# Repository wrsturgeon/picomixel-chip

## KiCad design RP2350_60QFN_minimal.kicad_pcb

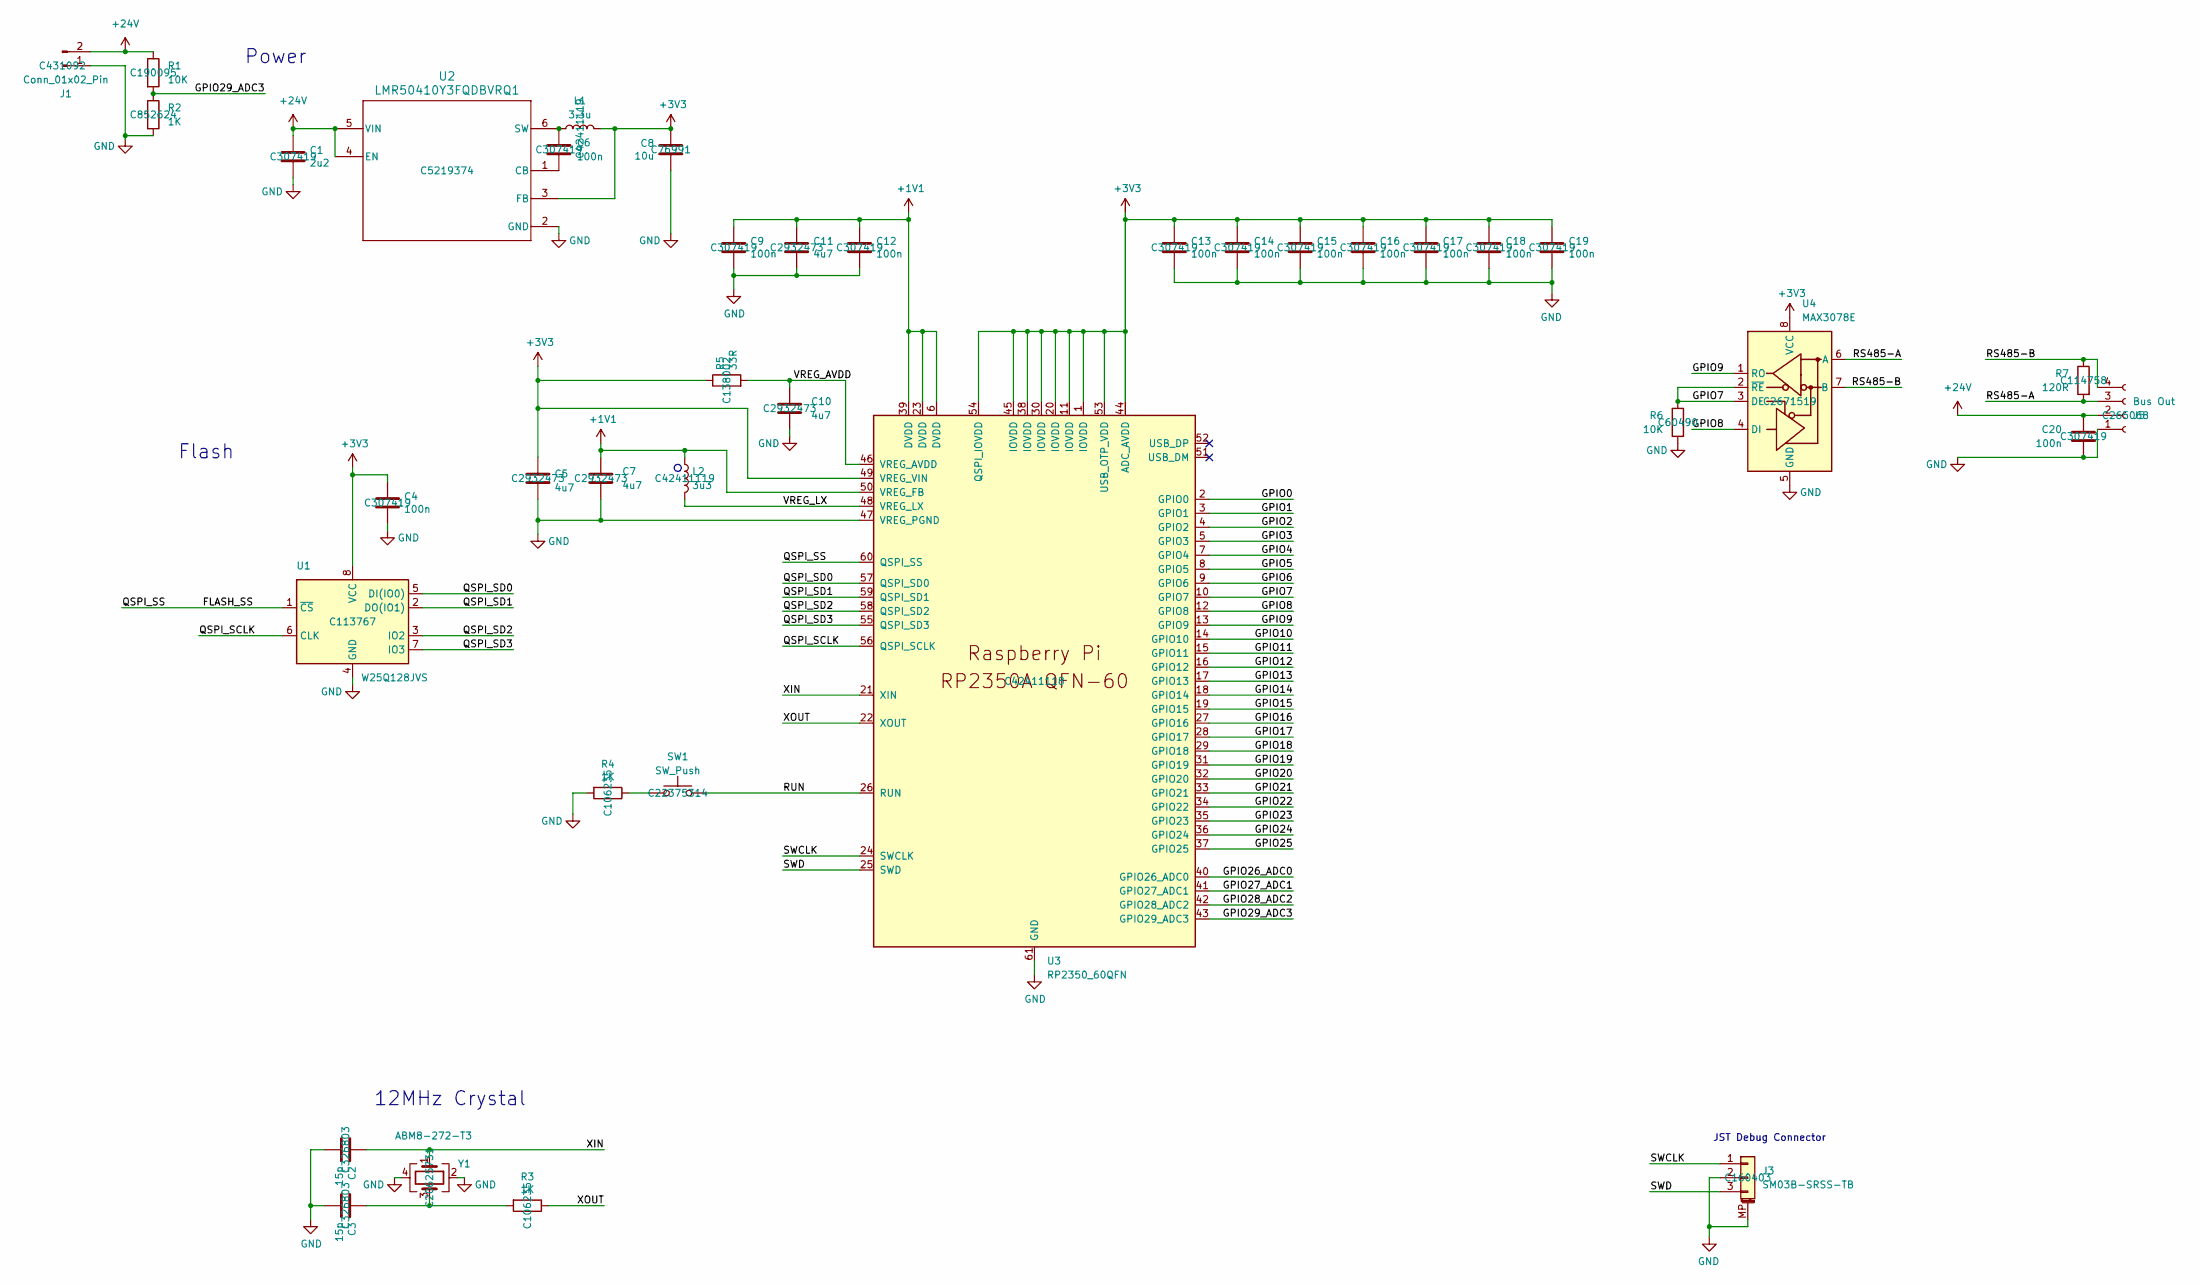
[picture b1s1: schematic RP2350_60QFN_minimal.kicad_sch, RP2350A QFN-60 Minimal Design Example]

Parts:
C1: 2u2; C_1206_3216Metric; LCSC Part # C307419
C2, C3: 15p; C_0402_1005Metric; LCSC Part # C326803
C4, C6, C9, C12, C13, C14, C16, C19, C20: 100n; C_0402_1005Metric; LCSC Part # C307419
C5, C7, C10, C11: 4u7; C_0402_1005Metric_small_pads; LCSC Part # C2932473
C8: 10u; C_0402_1005Metric; LCSC Part # C76991
C15, C17, C18: 100n; C_0402_1005Metric_small_pads; LCSC Part # C307419
J1: Conn_01x02_Pin; AMASS_XT30PW-M_1x02_P2.50mm_Horizontal; LCSC Part # C431092
J3: SM03B-SRSS-TB; JST_SH_SM03B-SRSS-TB_1x03-1MP_P1.00mm_Horizontal; LCSC Part # C160403
J5: Bus Out; JST_EH_S4B-EH_1x04_P2.50mm_Horizontal; LCSC Part # C265068
L1: 3.3u; L_pol_2016; LCSC Part # C42411119
L2: 3u3; L_pol_2016; LCSC Part # C42411119
R1: 10K; R_0402_1005Metric; LCSC Part # C190095
R2: 1K; R_0402_1005Metric; LCSC Part # C852624
R3, R4: 1K; R_0402_1005Metric; LCSC Part # C106235
R5: 33R; R_0402_1005Metric; LCSC Part # C138002
R6: 10K; R_0402_1005Metric; LCSC Part # C60490
R7: 120R; R_0402_1005Metric; LCSC Part # C114758
SW1: SW_Push; SW_Push_1P1T_NO_Vertical_Wuerth_434133025816; LCSC Part # C22375314
U1: W25Q128JVS; SOIC-8_5.3x5.3mm_P1.27mm; LCSC Part # C113767
U2: LMR50410Y3FQDBVRQ1; DBV0006A-MFG; LCSC Part # C5219374
U3: RP2350_60QFN; RP2350-QFN-60-1EP_7x7_P0.4mm_EP3.4x3.4mm_ThermalVias; LCSC Part # C42411118
U4: MAX3078E; SOIC-8_3.9x4.9mm_P1.27mm; LCSC Part # C2671519
Y1: ABM8-272-T3; Crystal_SMD_3225-4Pin_3.2x2.5mm; LCSC Part # C20625731

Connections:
+1V1: C7.1, C9.1, C11.1, C12.1, L2.1, U3.6 (DVDD), U3.23 (DVDD), U3.39 (DVDD), U3.50 (VREG_FB)
+3V3: C4.1, C5.1, C8.1, C13.1, C14.1, C15.1, C16.1, C17.1, C18.1, C19.1, L1.2, R5.1, U1.8 (VCC), U2.3 (FB), U3.1 (IOVDD), U3.11 (IOVDD), U3.20 (IOVDD), U3.30 (IOVDD), U3.38 (IOVDD), U3.44 (ADC_AVDD), U3.45 (IOVDD), U3.49 (VREG_VIN), U3.53 (USB_OTP_VDD), U3.54 (QSPI_IOVDD), U4.8 (VCC)
+24V: C1.1, C20.1, J1.2, J5.2, R1.1, U2.4 (EN), U2.5 (VIN)
/FLASH_SS: U1.1 (~CS), U3.60 (QSPI_SS)
/GPIO0: U3.2 (GPIO0)
/GPIO1: U3.3 (GPIO1)
/GPIO2: U3.4 (GPIO2)
/GPIO3: U3.5 (GPIO3)
/GPIO4: U3.7 (GPIO4)
/GPIO5: U3.8 (GPIO5)
/GPIO6: U3.9 (GPIO6)
/GPIO7: R6.1, U3.10 (GPIO7), U4.2 (~RE), U4.3 (DE)
/GPIO8: U3.12 (GPIO8), U4.4 (DI)
/GPIO9: U3.13 (GPIO9), U4.1 (RO)
/GPIO10: U3.14 (GPIO10)
/GPIO11: U3.15 (GPIO11)
/GPIO12: U3.16 (GPIO12)
/GPIO13: U3.17 (GPIO13)
/GPIO14: U3.18 (GPIO14)
/GPIO15: U3.19 (GPIO15)
/GPIO16: U3.27 (GPIO16)
/GPIO17: U3.28 (GPIO17)
/GPIO18: U3.29 (GPIO18)
/GPIO19: U3.31 (GPIO19)
/GPIO20: U3.32 (GPIO20)
/GPIO21: U3.33 (GPIO21)
/GPIO22: U3.34 (GPIO22)
/GPIO23: U3.35 (GPIO23)
/GPIO24: U3.36 (GPIO24)
/GPIO25: U3.37 (GPIO25)
/GPIO26_ADC0: U3.40 (GPIO26_ADC0)
/GPIO27_ADC1: U3.41 (GPIO27_ADC1)
/GPIO28_ADC2: U3.42 (GPIO28_ADC2)
/GPIO29_ADC3: R1.2, R2.1, U3.43 (GPIO29_ADC3)
/QSPI_SCLK: U1.6 (CLK), U3.56 (QSPI_SCLK)
/QSPI_SD0: U1.5 (DI(IO0)), U3.57 (QSPI_SD0)
/QSPI_SD1: U1.2 (DO(IO1)), U3.59 (QSPI_SD1)
/QSPI_SD2: U1.3 (IO2), U3.58 (QSPI_SD2)
/QSPI_SD3: U1.7 (IO3), U3.55 (QSPI_SD3)
/RS485-A: J5.3, R7.2, U4.6 (A)
/RS485-B: J5.4, R7.1, U4.7 (B)
/SWCLK: J3.1, U3.24 (SWCLK)
/SWD: J3.3, U3.25 (SWD)
/VREG_AVDD: C10.1, R5.2, U3.46 (VREG_AVDD)
/VREG_LX: L2.2, U3.48 (VREG_LX)
/XIN: C2.1, U3.21 (XIN), Y1.1
/XOUT: R3.1, U3.22 (XOUT)
GND: C1.2, C2.2, C3.2, C4.2, C5.2, C7.2, C8.2, C9.2, C10.2, C11.2, C12.2, C13.2, C14.2, C15.2, C16.2, C17.2, C18.2, C19.2, C20.2, J1.1, J3.2, J3.MP (MountPin), J5.1, R2.2, R4.2, R6.2, U1.4 (GND), U2.2 (GND), U3.47 (VREG_PGND), U3.61 (GND), U4.5 (GND), Y1.2, Y1.4
unnamed: C3.1, R3.2, Y1.3
unnamed: C6.2, U2.1 (CB)
unnamed: C6.1, L1.1, U2.6 (SW)

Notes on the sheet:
JST Debug Connector
Flash
12MHz Crystal
Power

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
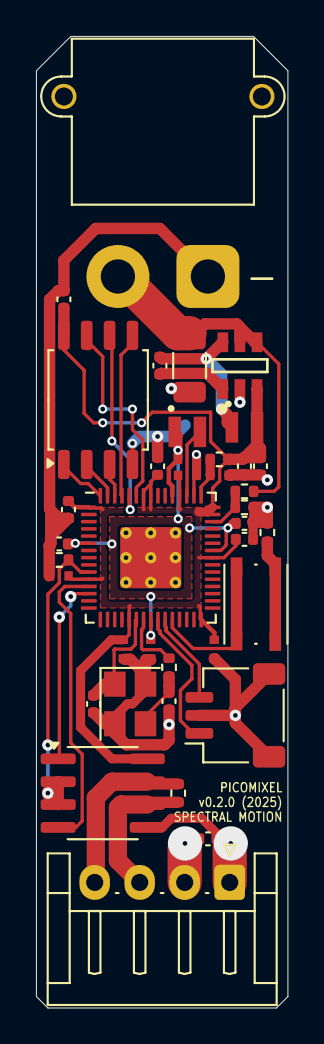
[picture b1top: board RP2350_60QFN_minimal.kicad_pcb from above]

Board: 2 copper layers, 14.0 x 54.0 mm, 38 parts (0 on the bottom side), 27 nets.

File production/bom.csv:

Designator,Footprint,Quantity,Value,LCSC Part #
C1,1206,1,2u2,C307419
"C10, C11, C5, C7",0402,4,4u7,C2932473
"C12, C13, C14, C15, C16, C17, C18, C19, C20, C4, C6, C9",0402,12,100n,C307419
"C2, C3",0402,2,15p,C326803
C8,0402,1,10u,C76991
J1,AMASS_XT30PW-M_1x02_P2.50mm_Horizontal,1,Conn_01x02_Pin,C431092
J3,JST_SH_SM03B-SRSS-TB_1x03-1MP_P1.00mm_Horizontal,1,SM03B-SRSS-TB,C160403
J5,JST_EH_S4B-EH_1x04_P2.50mm_Horizontal,1,Bus Out,C265068
L1,L_pol_2016,1,3.3u,C42411119
L2,L_pol_2016,1,3u3,C42411119
R1,0402,1,10K,C190095
R2,0402,1,1K,C852624
"R3, R4",0402,2,1K,C106235
R5,0402,1,33R,C138002
R6,0402,1,10K,C60490
R7,0402,1,120R,C114758
SW1,SW_Push_1P1T_NO_Vertical_Wuerth_434133025816,1,SW_Push,C22375314
U1,SOIC-8_5.3x5.3mm_P1.27mm,1,W25Q128JVS,C113767
U2,DBV0006A-MFG,1,LMR50410Y3FQDBVRQ1,C5219374
U3,RP2350-QFN-60-1EP_7x7_P0.4mm_EP3.4x3.4mm_ThermalVias,1,RP2350_60QFN,C42411118
U4,SOIC-8_3.9x4.9mm_P1.27mm,1,MAX3078E,C2671519
Y1,Crystal_SMD_3225-4Pin_3.2x2.5mm,1,ABM8-272-T3,C20625731

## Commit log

2025-04-07 Unedited `.zip` from `https://datasheets.raspberrypi.com/rp2350/hardware-design-with-rp2350.pdf`
2025-04-07 Save without editing to update KiCAD version
2025-04-09 Decent core PCB setup, considering removing USB to make space for flash
2025-04-09 fucking reversed polarity on the XT30
2025-04-10 Finished design without wifi & unchecked
2025-04-10 Finished, checked design (still no WiFi)
2025-04-10 Find parts on LCSC
2025-04-10 Export finished
2025-04-10 All parts in stock
